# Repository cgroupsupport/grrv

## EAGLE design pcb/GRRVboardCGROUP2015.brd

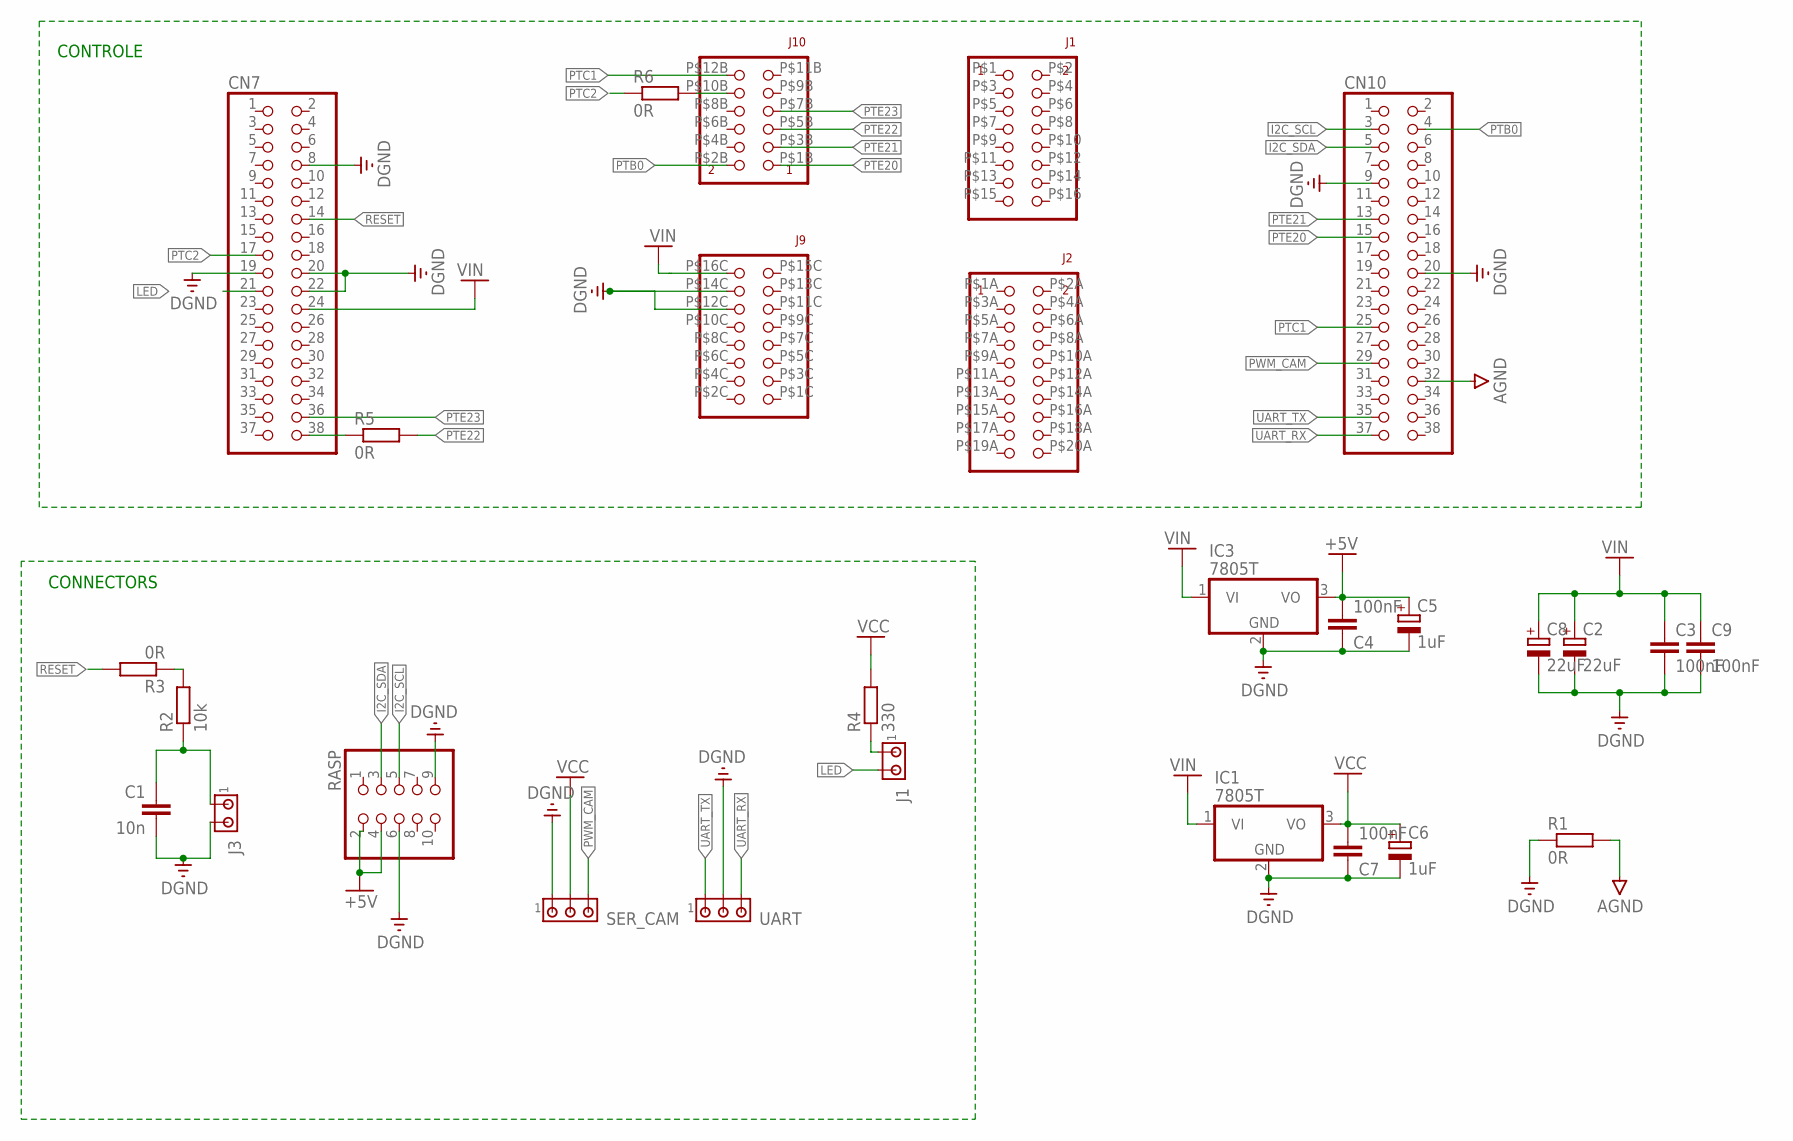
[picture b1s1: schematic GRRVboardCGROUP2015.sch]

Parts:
C1: 10n; C0805
C2, C8: 22uF; SMC_B
C3, C4, C7, C9: 100nF; C0805
C5, C6: 1uF; SMC_B
CN7, CN10: PINHD-2X19; 2X19
IC1, IC3: 7805T; TO220H
J1, J3: MTA02-100; 10X02MTA
R1: 0R; M1206
R2: 10k; M0805
R3, R5, R6: 0R; R0805
R4: 330; M0805
RASP: PINHD-2X5; 2X05
SER_CAM: MTA03-100; 10X03MTA
U$1: FRDM-TFC; FRDM
UART: MTA03-100; 10X03MTA

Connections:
+5V: C4.2, C5.+, IC3.3 (VO), RASP.2, RASP.4
AGND: CN10.32, R1.2
DGND: C1.2, C2.-, C3.2, C4.1, C5.-, C6.-, C7.1, C8.-, C9.2, CN7.8, CN7.19, CN7.20, CN7.22, CN10.9, CN10.20, IC1.2 (GND), IC3.2 (GND), J3.2, R1.1, RASP.6, RASP.9, SER_CAM.1, U$1.P$12C (12C), U$1.P$14C (14C), UART.2
I2C_SCL: CN10.3, RASP.5
I2C_SDA: CN10.5, RASP.3
LED: CN7.21, J1.2
unnamed: CN7.38, R5.1
unnamed: R2.2, R3.1
unnamed: J1.1, R4.1
unnamed: R6.2, U$1.P$10B (10B)
unnamed: C1.1, J3.1, R2.1
PTB0: CN10.4, U$1.P$2B (2B)
PTC1: CN10.25, U$1.P$12B (12B)
PTC2: CN7.17, R6.1
PTE20: CN10.15, U$1.P$1B (1B)
PTE21: CN10.13, U$1.P$3B (3B)
PTE22: R5.2, U$1.P$5B (5B)
PTE23: CN7.36, U$1.P$7B (7B)
PWM_CAM: CN10.29, SER_CAM.3
RESET: CN7.14, R3.2
UART_RX: CN10.37, UART.3
UART_TX: CN10.35, UART.1
VCC: C6.+, C7.2, IC1.3 (VO), R4.2, SER_CAM.2
VIN: C2.+, C3.1, C8.+, C9.1, CN7.24, IC1.1 (VI), IC3.1 (VI), U$1.P$16C (16C)

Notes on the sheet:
CONTROLE
CONNECTORS

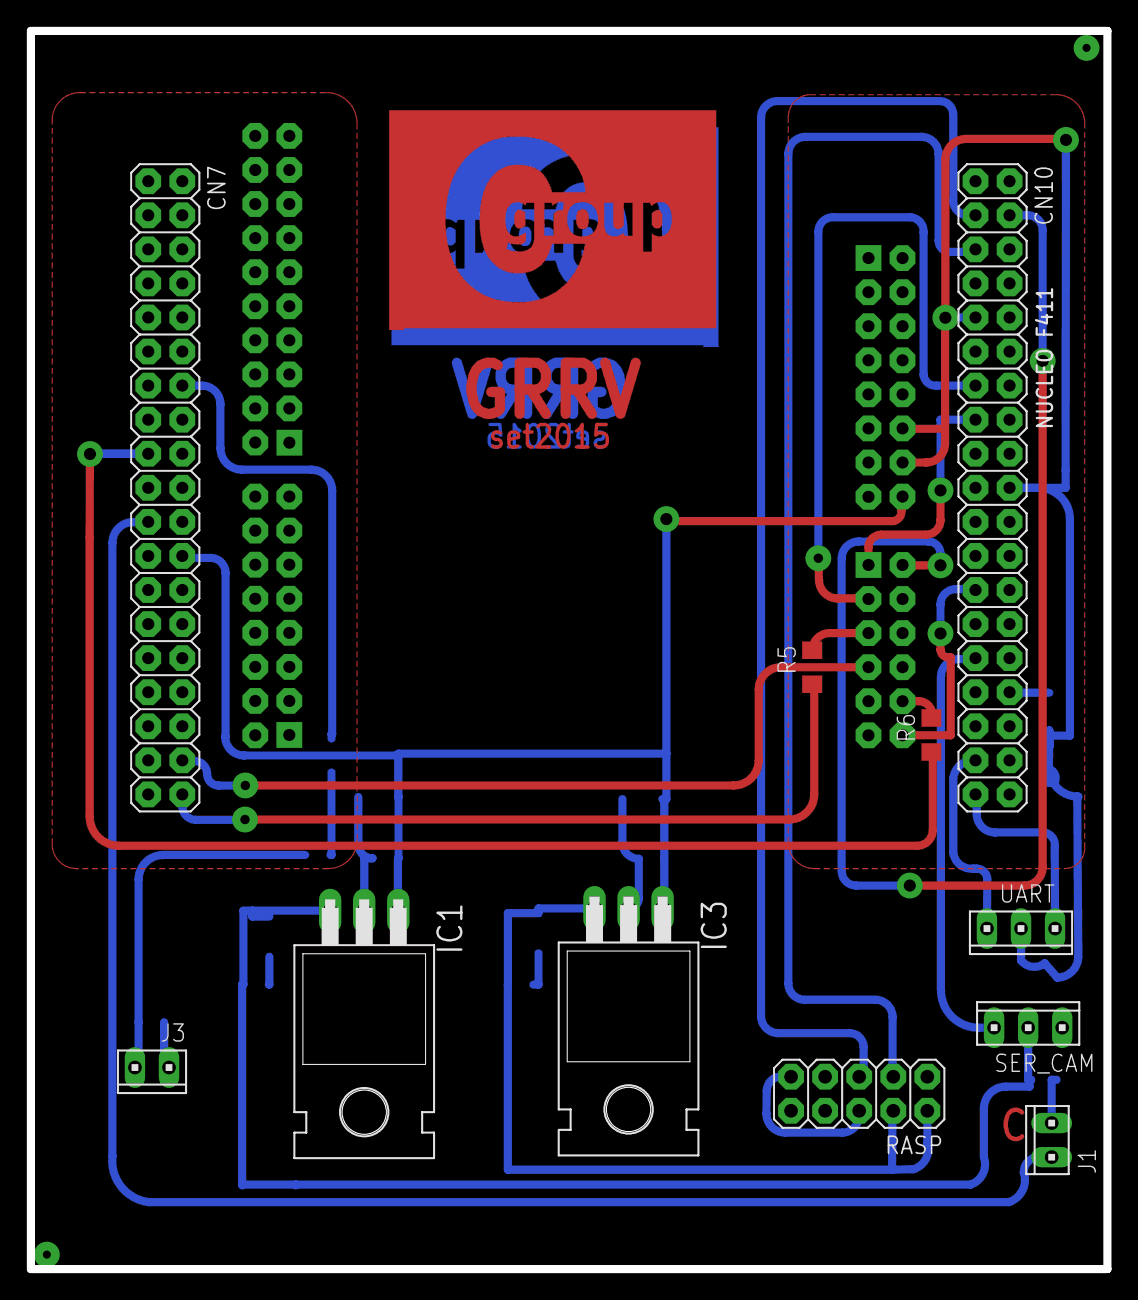
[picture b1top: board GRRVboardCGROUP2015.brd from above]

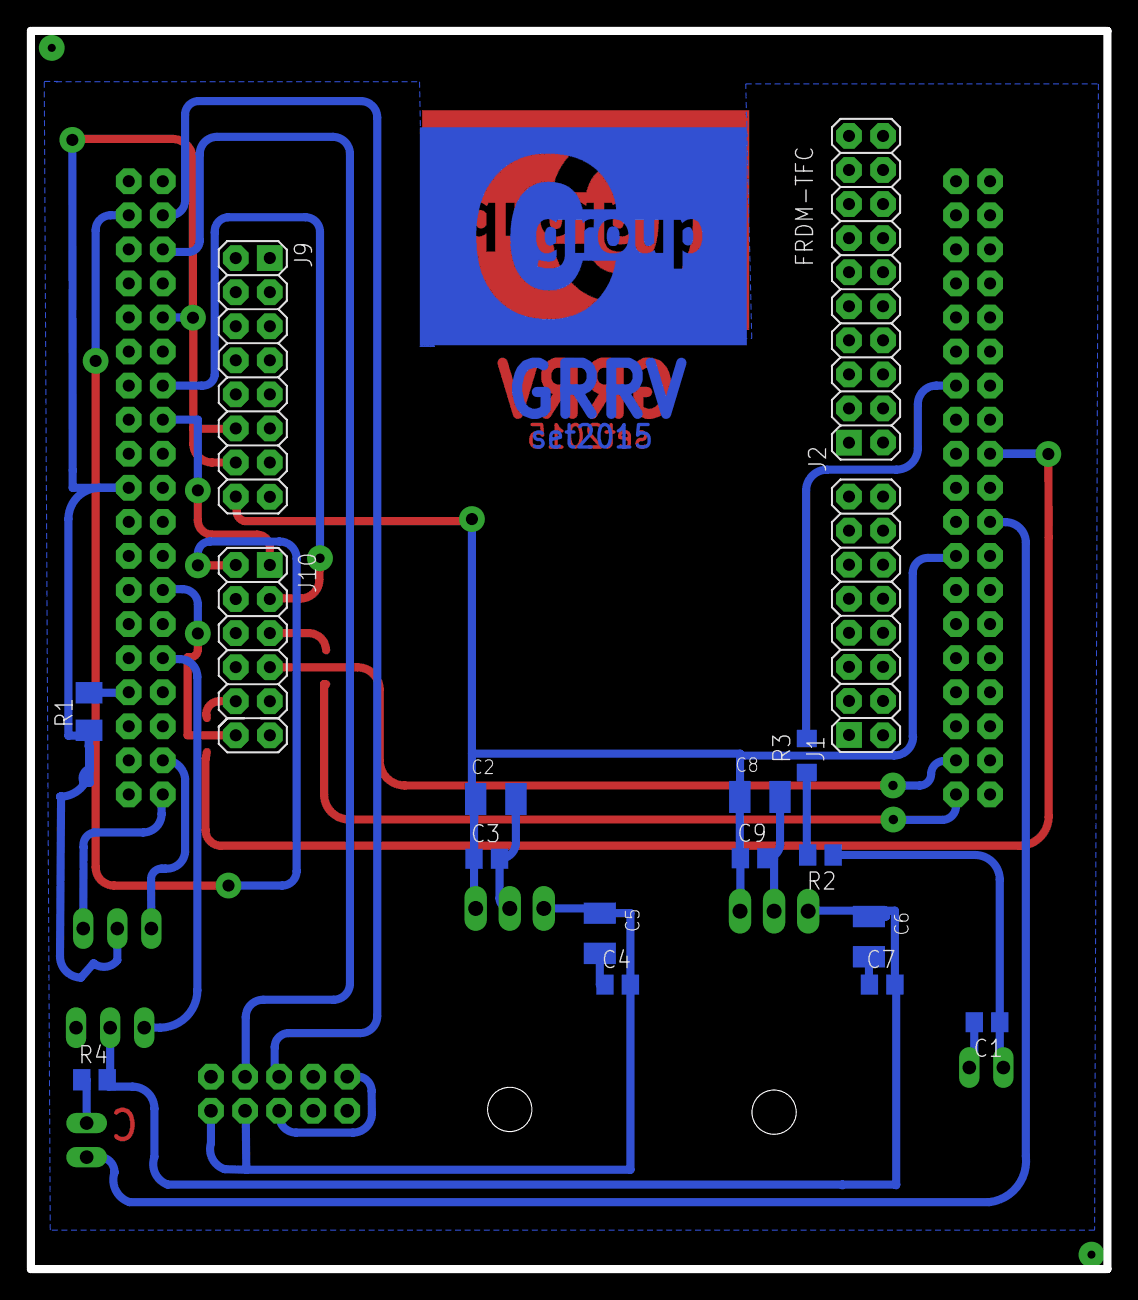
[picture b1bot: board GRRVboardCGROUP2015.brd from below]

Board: 2 copper layers, 80.3 x 92.3 mm, 25 parts (14 on the bottom side), 24 nets.

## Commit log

2015-10-06 Add automation

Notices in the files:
parts and their libraries:
supply0: Copyright (C) 2007, Bob Starr
